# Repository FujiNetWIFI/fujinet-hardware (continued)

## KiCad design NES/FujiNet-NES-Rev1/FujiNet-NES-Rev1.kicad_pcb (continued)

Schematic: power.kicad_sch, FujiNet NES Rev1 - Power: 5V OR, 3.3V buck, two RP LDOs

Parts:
C51, C55, C56: 100nF; C_0603_1608Metric; MPN CC0603KRX7R9BB104; LCSC C14663
C52, C53, C54, C57, C58: 22uF; C_0805_2012Metric; MPN CL21A226MAQNNNE; LCSC C45783
C59, C60, C61, C62: 1uF; C_0603_1608Metric; MPN CL10A105KB8NNNC; LCSC C15849
D7: SS34; D_SMA; MPN SS34; LCSC C8678
L3: 6.8uH; L_Sunlord_SWPA4030S; MPN SWPA4030S6R8MT; LCSC C62684
Q1: AO3401A; SOT-23; MPN AO3401A; LCSC C15127
R25: 4.7k; R_0603_1608Metric; MPN 0603WAF4701T5E; LCSC C23162
U7: AP63203WU; TSOT-23-6; MPN AP63203WU-7; LCSC C780769
U8, U9: AP2112K-3.3; SOT-23-5; MPN AP2112K-3.3TRG1; LCSC C51118

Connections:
+3V3: C57.1, C58.1, L3.2, U7.1 (FB); also elsewhere on the board
+3V3_RP: C60.1, U8.5 (VOUT); also elsewhere on the board
+3V3_RPB: C62.1, U9.5 (VOUT); also elsewhere on the board
+5V: C52.1, C53.1, C54.1, C55.1, C59.1, C61.1, D7.1 (K), Q1.2 (S), U7.2 (EN), U7.3 (IN), U8.1 (VIN), U8.3 (EN), U9.1 (VIN), U9.3 (EN); also elsewhere on the board
BUCK_BST: C56.2, U7.6 (BST)
BUCK_SW: C56.1, L3.1, U7.5 (SW)
CONS_5V: C51.1, Q1.3 (D); also elsewhere on the board
GND: C51.2, C52.2, C53.2, C54.2, C55.2, C57.2, C58.2, C59.2, C60.2, C61.2, C62.2, R25.2, U7.4 (GND), U8.2 (GND), U9.2 (GND); also elsewhere on the board
VBUS: D7.2 (A), Q1.1 (G), R25.1; also elsewhere on the board

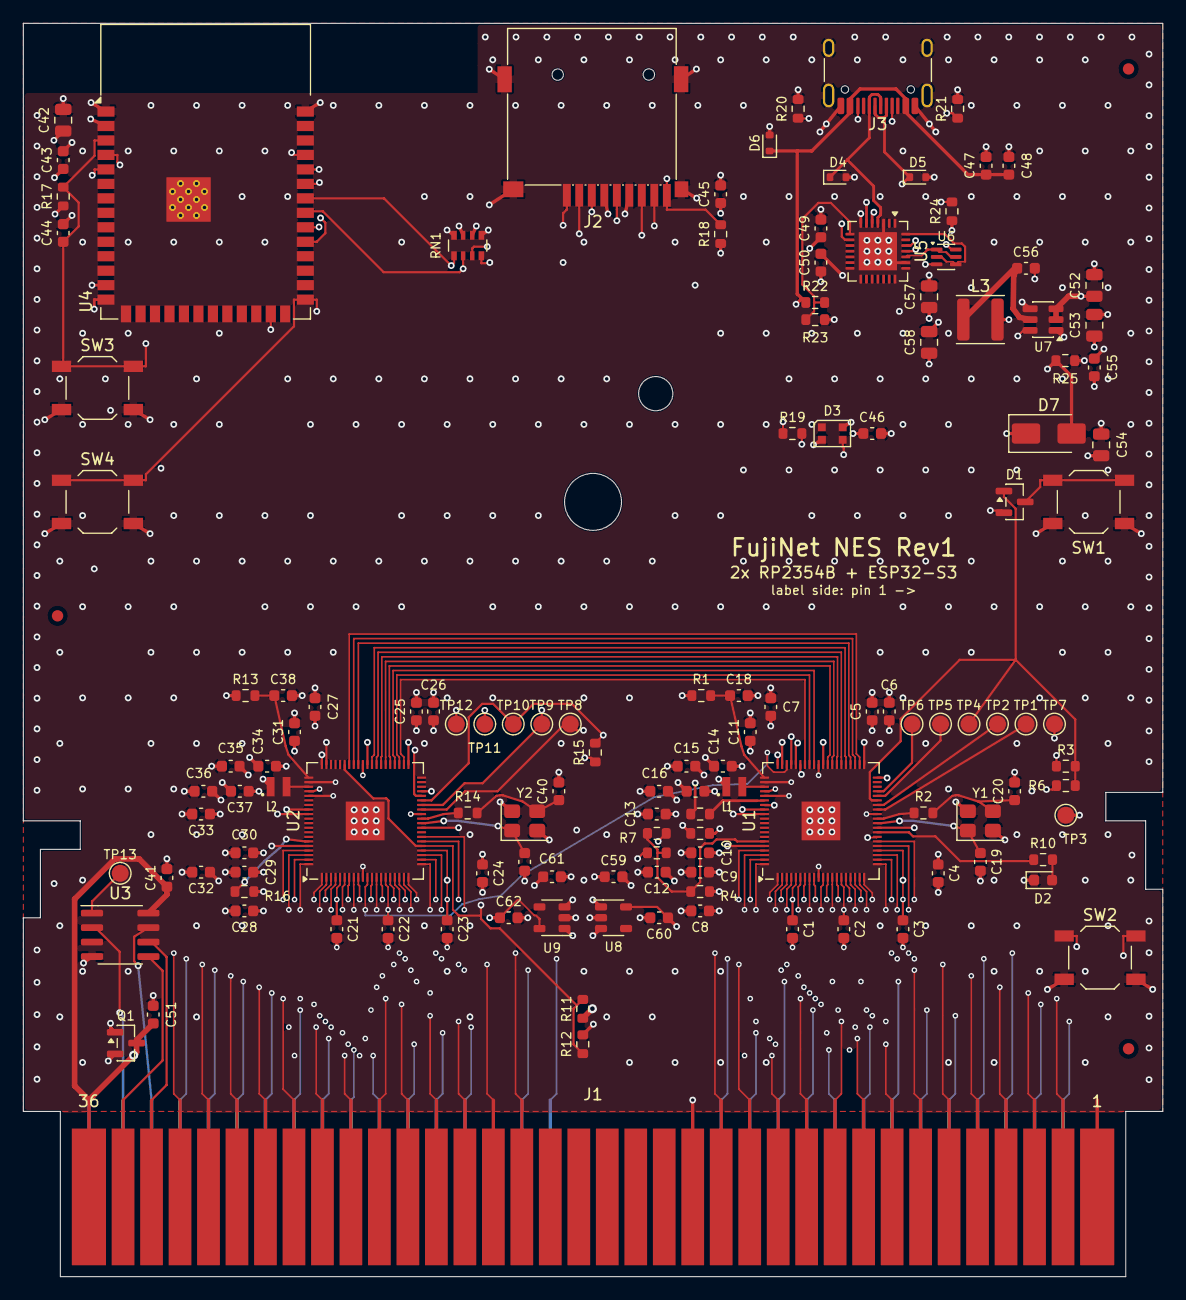
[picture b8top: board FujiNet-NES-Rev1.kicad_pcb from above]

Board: 6 copper layers, 100.0 x 110.0 mm, 133 parts (0 on the bottom side), 134 nets.

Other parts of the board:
FID1, FID2, FID3: Fiducial_1mm_Mask2mm

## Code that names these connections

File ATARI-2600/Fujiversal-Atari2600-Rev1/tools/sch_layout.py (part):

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    P = lambda n: sh.P(U, n)
    gp = lambda g: sh.P(U, D.RP_GPIO_PIN[g])
    xg = gp(2)[0]                                       # the GPIO column (pin ends), facing left
    # ---- the edge, level with GPIO2..22
    jx = X - 78.74
    sh.place(J, jx, 0)
    jy = gp(2)[1] - sh.N(J, 'CA0')[1]                    # A0 level with GPIO2
    sh.place(J, jx, jy, fields='left')
    sh.sup(sh.P(J, 23), 'CONS_5V')
    g1, g2 = sh.P(J, 12), sh.P(J, 24)
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        y = by + 5.08 * k
        sh.bus((bx, y), (bx + 7.62, y))
        sh.glabel(Pt_(bx + 7.62, y, 1, 0), name, 'R', shape)
    # ---- debug UART (GPIO0/1) up to two test pads, above the bus
    for g, x, tp, fl in ((0, xg - 5.08, 'TP_TX', 'left'), (1, xg - 15.24, 'TP_RX', 'left')):
        p = gp(g)
        sh.wire(p, (x, p[1]), (x, Y - 50.8))
        sh.place(K[tp], x, Y - 50.8, fields=fl)
    sh.name((xg - 5.08, Y - 45.72), 'RP_TX', 'R', 'R')
    sh.name((xg - 15.24, Y - 45.72), 'RP_RX', 'L', 'L')
    # ---- below the bus: the activity LED (GPIO25) and the console 5 V sense (GPIO27)
    p = gp(25)
    x = xg - 12.7
    rl, dl = K['R_LED'], K['D_LED']
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    sh.name(sh.P(rl, 2), 'RP_LED_A', 'L', 'L')
    p = gp(27)
    sh.wire(p, (xg - 5.08, p[1]), (xg - 5.08, Y + 40.64))
    sh.glabel(Pt_(xg - 5.08, Y + 40.64, 0, 1), 'VSENSE', 'D', 'input')
    for g in (23, 24, 26, 28, 29):
        sh.nc(gp(g))
    # ---- supplies across the top: the +3V3_RP rail and its decoupling row (right),
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    sh.wire(*sorted({(q[0], ry) for q in rail_pins} | {(av[0], ry)} | {(x, ry) for x in xs}))
    sh.sup((rail_pins[0][0], ry), '+3V3_RP')
    # core regulator: LX up and left through the inductor, DVDD on to its caps;
    # FB and the DVDD pins join that node
    lx, fb, dv = P(48), P(50), P(6)
    ly = top - 25.4
    L = K['L_VREG']
    sh.place(L, lx[0] - 7.62, ly, rot=90, fields='below')         # pin 1 (DVDD) left, pin 2 (LX) right
    sh.wire(lx, (lx[0], ly), sh.P(L, 2))
    dcaps = [K[k] for k in ('C_VOUT', 'C_DVDD39', 'C_DVDD6', 'C_DVDD23')]
    node = (dv[0] - 10.16, ly)
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    sh.place(D1, xr + 20.32, ry_ - 7.62, rot=180, mirror='y', fields='below')   # A1 left, A2 right, K up
    sh.wire(pts[1], sh.P(D1, 1))
    sh.wire(sh.P(D1, 2), (col, sh.P(D1, 2)[1]))
    sh.glabel((col, sh.P(D1, 2)[1]), 'S3_EN', 'R', 'bidirectional')
    k = sh.P(D1, 3)
    sw = K['SW_RESET']
    sh.place(sw, xr + 27.94, ry_ - 17.78, fields='above')
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    sh.gnd((xr + 38.1, ry_ - 17.78))
    sh.name((k[0], ry_ - 15.24), 'RST_BTN', 'R', 'R')
    rc = K['R_RUNCTL']
    sh.place(rc, pts[2][0] + 3.81, ry_, rot=270, fields='above')     # pin 2 (RUN) left, pin 1 right
    sh.wire(pts[2], sh.P(rc, 2))
    sh.wire(sh.P(rc, 1), (col, ry_))
    sh.glabel((col, ry_), 'RUN_CTL', 'R', 'input')
    sh.name((xr + 2.54, ry_), 'RUN', 'D', 'R')
    # USB to the S3: 27R series pair
    for pin, r, net, rnet, d in ((51, 'R_USBM', 'USB_DM', 'RP_USB_DM', 'U'), (52, 'R_USBP', 'USB_DP', 'RP_USB_DP', 'D')):
        p = P(pin)
        rr = K[r]
        sh.place(rr, xr + 38.1, p[1], rot=270, fields='above' if pin == 51 else 'below')
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    sh.place(sc, pts[2][0] + 3.81, q, rot=270, fields='above')
    sh.wire(pts[2], sh.P(sc, 2))
    sh.wire(sh.P(sc, 1), (col, q))
    sh.glabel((col, q), 'BOOTSEL_CTL', 'R', 'input')
    for n in (55, 56, 57, 58, 59):
        sh.nc(P(n))
    # 12 MHz crystal: XIN straight to the crystal and its load cap, XOUT through the 1k
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    g2 = sh.P(Yc, 2)
    sh.wire(g2, (g2[0] + 2.54, g2[1]))
    sh.gnd((g2[0] + 2.54, g2[1]))
    sh.place(rx, xr + 10.16, xo[1], rot=90, fields='above')        # pin 1 (XOUT) left
    sh.wire(xo, sh.P(rx, 1))
    sh.wire(sh.P(rx, 2), (cx, xo[1]), sh.P(Yc, 3))
    sh.place(c2, cx, xo[1] + 3.81, fields='right')
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    en = sh.P(U, 3)
    ey = 109.22
    sh.wire(en, (170.18, en[1]), (170.18, ey), (162.56, ey), (152.4, ey), (142.24, ey), (127.0, ey))
    sh.glabel((127.0, ey), 'S3_EN', 'L', 'bidirectional')
    sh.place(K['R_EN'], 162.56, ey - 3.81, fields='right')
    sh.sup(sh.P(K['R_EN'], 1), '+3V3')
    sh.place(K['C_EN'], 152.4, ey + 3.81, fields='right')
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    # IO0 (BOOT): button + the auto-program transistor
    io0 = sh.P(U, 27)
    sh.wire(io0, (147.32, io0[1]), (137.16, io0[1]))
    sh.glabel((137.16, io0[1]), 'S3_IO0', 'L', 'bidirectional')
    sh.place(K['SW_S3BOOT'], 147.32, io0[1] + 5.08, rot=270, fields='left')
    sh.gnd(sh.P(K['SW_S3BOOT'], 2))
    # IO4 / IO5: RUN / BOOTSEL of the RP2354A
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    sh.place(K['R_CPRST'], 172.72, rst[1] - 3.81, fields='left')
    sh.wire(rst, (172.72, rst[1]), (167.64, rst[1]))
    sh.sup(sh.P(K['R_CPRST'], 1), '+3V3')
    sh.glabel((167.64, rst[1]), 'CP_RST', 'L')
    sh.gnd(sh.P(U, 3))
    sh.gnd(sh.P(U, 23), 2.54, rot=90)                      # /CTS tied low
    nc_unused(sh, U)
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    gq = sh.P(K['C_CONS'], 2)
    sh.wire(gq, (gq[0] - 5.08, gq[1]))
    sh.flag((gq[0] - 5.08, gq[1]), 'GND')
    # console 5 V sense for the RP (GPIO27): 0.6 x CONS_5V, filtered
    vh, vl, vc = K['R_VSH'], K['R_VSL'], K['C_VS']
    sh.place(vh, 53.34, y5 - 7.62 - 3.81, rot=180, fields='left')   # pin 1 (CONS_5V) down
    sh.wire((53.34, y5), sh.P(vh, 1))
    nd = sh.P(vh, 2)
    vy = nd[1] - 2.54
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    sh.gnd(sh.P(vl, 2))
    sh.place(vc, 73.66, vy + 3.81, fields='right')
    sh.gnd(sh.P(vc, 2))
    sh.glabel((83.82, vy), 'VSENSE', 'R', 'output')
    # USB VBUS -> gate, and through the SS34 onto +5V
    Dv = K['D_VBUS']
    sh.place(Dv, 83.82, yv, rot=180, fields='below')
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
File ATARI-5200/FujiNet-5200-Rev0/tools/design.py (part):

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RP_IO_RAIL = '+3V3_RP'     # IOVDD x8, QSPI_IOVDD, USB_OTP_VDD, ADC_AVDD: the fast LDO
RP_CORE_RAIL = RP_IO_RAIL  # VREG_VIN (+ VREG_AVDD through 33R) on the same LDO rail

# a52_cart.h.  GPIO0-31 are the 5 V-tolerant bus inputs; GPIO40-47 are not and carry only the ADC
# sense and the 3.3 V debug header.
RP_GPIO_NET = {i: 'A%d' % i for i in range(14)}                     # A0_PIN 0: A0-A13
RP_GPIO_NET.update({14: 'EN40_N', 15: 'EN80_N'})                    # EN40_PIN, EN80_PIN
RP_GPIO_NET.update({16 + i: 'RP_D%d' % i for i in range(8)})        # D0_PIN 16: into the '541
RP_GPIO_NET.update({24: 'PWR_OK', 25: 'PHI2_RP', 26: 'BUF_EN', 27: 'RP_LED', 28: 'ILK'})
RP_GPIO_NET.update({g: NC for g in range(29, 40)})
RP_GPIO_NET.update({40: 'VSENSE_ADC', 41: NC, 42: NC, 43: NC, 44: 'DBG_TX', 45: 'DBG_RX', 46: NC, 47: NC})
assert len(RP_GPIO_NET) == 48 and set(RP_GPIO_NET) == set(RP_GPIO_PIN)

# ESP32-S3-WROOM-1 module pad -> function (pads per the KiCad symbol)
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      70: NC, 71: NC, 72: NC, 73: NC, 74: NC,                                 # QSPI (flash in package)
      75: 'QSPI_SS', 81: 'GND'}
rp.update({p: RP_IO_RAIL for p in RP_IOVDD_PINS})
rp.update({p: 'DVDD' for p in RP_DVDD_PINS})
for g, pin in RP_GPIO_PIN.items():
    rp[pin] = RP_GPIO_NET[g]
U_RP = add('U', '%s:RP2354B_Split' % LIB, 'RP2354B', FP('QFN-80-1EP_10x10mm_P0.4mm_EP3.4x3.4mm'), rp,
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U_RP.unit_sheets = {1: 'cart-bus', 2: 'rp-core'}
U_RP.pin_unit = {str(pad): 1 if pad in RP_GPIO_PIN.values() else 2 for pad in rp}

# -- the data path: the RP puts each byte on GPIO16-23, a 74HCT541 that only the enables open puts
# it on D0-D7 (a52_cart.h: software is never between an enable and the data).  Its eight channels
# are identical, so they are used in reverse (bit k on channel 8-k: A8 / Y8 carry D0): turned 270
# degrees over the D0-D7 fingers, the '541's Y row (pins 11-18) then meets the fingers in their own
# left-to-right order and its A row (pins 9-2) the RP2354B's GPIO16-23 corner in theirs -- the data
# path from the slot to the RP crosses nothing (gen_pcb.buf_fanin draws the finger side).
buf = {1: 'SERVE_N', 19: 'EN_ANY_N', 10: 'GND', 20: '+5V'}     # /OE1, /OE2 (equivalent: drive = !OE1 & !OE2)
buf.update({9 - i: 'RP_D%d' % i for i in range(8)})             # A8..A1 (pins 9..2) = bit 0..7
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# -- PHI2 (edge 14): GND on CA018087; on the universal boards PHI2 through a 74LS125 and CR9 (1N914,
# anode at pin 14), so the console only pulls it low, to VOL(LS125) + VF(1N914) <= ~1.15 V: over the
# RP2350's VIL of 0.8 V (Table 1436).  A 74LVC1G17 Schmitt on +5V reads it (VT- >= 1.32 V at VCC
# 4.5 V, Nexperia 74LVC1G17 Table 8) and drives GPIO25 (5 V tolerant).  The pull-up comes from the
# console's own 5 V, so nothing is pushed into an unpowered console; 4.7k reaches VT+ in ~60 ns.
R('4.7k', 'CONS_5V', 'PHI2', desc='PHI2 pull-up (the console drives pin 14 only low, through a diode)',
  key='R_PHI2PU')
add('U', '74xGxx:74LVC1G17', '74LVC1G17', FP('SOT-353_SC-70-5'), {1: NC, 2: 'PHI2', 3: 'GND', 4: 'PHI2_RP',
    5: '+5V'}, mpn='74LVC1G17GW,125', lcsc='C426705', desc='PHI2 Schmitt buffer: CMOS thresholds for the '
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       key='JP_ILK')
# DNP: a firmware-controlled interlock (a console power cycle = its only reset).  The jumper sits at
# ground potential when closed, so the switch is an N-FET on the low side: D on CI2 (pin 36), S on CI1
# (pin 18), gate pulled up to +5V (closed whenever the cart has power); GPIO28 high turns Q_ILKDRV on
# and opens it.  Needs the cart powered from USB or the edge's raw DC once JP_ILK is cut.
NFET('ILK_G', 'ILK_A', 'ILK_B', 'interlock switch (DNP): D = CI2 (pin 36), S = CI1 (pin 18)', dnp=True,
     key='Q_ILK')
R('10k', '+5V', 'ILK_G', desc='interlock switch closed by default (DNP)', dnp=True, key='R_ILKG')
NFET('ILK', 'GND', 'ILK_G', 'interlock switch driver, G = GPIO28: high opens the interlock (DNP)', dnp=True,
     key='Q_ILKDRV')
R('4.7k', 'ILK', 'GND', desc='GPIO28 low until the firmware drives it (RP2350-E9: <= 8.2k; DNP)', dnp=True,
  key='R_ILKPD')
# -- VR1 (the console 5 V that feeds the cart) for the ADC (GPIO40, not 5 V tolerant): 100k / 100k =
# 0.5 x, 5.5 V reads 2.75 V; 100 nF for the ADC's sample capacitor
R('100k', 'CONS_5V', 'VSENSE_ADC', desc='console 5V -> ADC divider (0.5 x)', key='R_ADCH')
R('100k', 'VSENSE_ADC', 'GND', desc='console 5V -> ADC divider', key='R_ADCL')
C('100nF', 'VSENSE_ADC', desc='ADC sample reservoir', key='C_ADCF')
# -- activity LED straight off GPIO27 (3.3 V): red, ~1.3 mA
R('1k', 'RP_LED', 'RP_LED_A', desc='activity LED series', key='R_LED')
add('D', 'Device:LED', 'red', FP('LED_0603_1608Metric'), {1: 'GND', 2: 'RP_LED_A'},
    mpn='KT-0603R', lcsc='C2286', desc='activity LED (GPIO27)', key='D_LED')
# -- debug UART (GPIO44 TX, GPIO45 RX; 3.3 V only), DNP: fit for bring-up
add('J', 'Connector_Generic:Conn_01x03', 'DBG UART', FP('PinHeader_1x03_P2.54mm_Vertical'),
    {1: 'DBG_TX', 2: 'DBG_RX', 3: 'GND'}, mpn='PZ254V-11-03P', lcsc='C2937625',
    desc='RP debug UART, 3.3 V: 1 TX (GPIO44), 2 RX (GPIO45), 3 GND; fit for bring-up', dnp=True, key='J_DBG')
# -- bring-up pads: the enables, PHI2 and the '541's two enables, PWR_OK, with a scope ground
TP('EN40_N', '/EN40', desc='scope pad: console /Enable $40-$7F', key='TP_EN40')
TP('EN80_N', '/EN80', desc='scope pad: console /Enable $80-$BF', key='TP_EN80')
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C('10uF', RP_IO_RAIL, desc='RP IO rail bulk (LDO output)', key='C_IOBULK')
C('4.7uF', RP_CORE_RAIL, desc='VREG_VIN bulk (LDO rail)', key='C_VREGIN')
for pin in RP_DVDD_PINS:
    C('100nF', 'DVDD', desc='DVDD decoupling', key='C_DV%d' % pin)
C('4.7uF', 'DVDD', desc='core regulator output', key='C_DVBULK')
R('33R', RP_CORE_RAIL, 'VREG_AVDD', desc='VREG_AVDD filter', key='R_AVDD')
C('4.7uF', 'VREG_AVDD', desc='VREG_AVDD filter', key='C_AVDD')
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SW('RESET', 'RST_BTN', 'cart RESET: RP RUN + S3 EN via BAT54C', key='SW_RESET')
add('D', 'Diode:BAT54C', 'BAT54C', FP('SOT-23'), {1: 'RUN', 2: 'S3_EN', 3: 'RST_BTN'},
    mpn='BAT54C,215', lcsc='C37704', desc='RESET steering, common cathode', key='D_RST')
# RUN / BOOTSEL: the S3 drives them low to assert (fnPicoUpdater::forceBootselViaPins)
R('10k', RP_IO_RAIL, 'RUN', desc='RUN pull-up', key='R_RUN')
R('10k', RP_IO_RAIL, 'QSPI_SS', desc='QSPI_SS pull-up', key='R_SS')
R('1k', 'QSPI_SS', 'BOOTSEL_BTN', desc='BOOTSEL button series', key='R_BSEL')
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
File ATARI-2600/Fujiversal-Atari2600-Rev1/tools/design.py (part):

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~/Workspace/fn-2600):
  pico/atari-2600/firmware/include/vcs_pins.h       A0-A12 GP2-14, D0-D7 GP15-22
  pico/atari-2600/firmware/boards/fujivcs.h         LED = PICO_DEFAULT_LED_PIN (GP25)
  include/pinmap/fujiversal-atari2600.h             S3 pins (SD, LED, UART0, RUN/BOOTSEL)
Edge pinout: the standard 2600 24-pin cartridge port; geometry and face
orientation from the FujiPlusCart prototype gerbers (make_edge_fp.py).

What changed from Rev0 (RP2040 + W25Q16 + 3x 74LVC245A):
  * RP2354A (RP2350A + 2 MB flash stacked in the package), wired straight to
    the 5 V edge.  Its GPIO0-25 are "Digital IO (FT)": they tolerate 5.5 V
    while IOVDD is 3.3 V (RP2350 datasheet, pin types / VPIN_FT), and a 3.3 V
    high clears the 6507's TTL VIH (2.0 V).  No buffers, so no DIR pin: the
    firmware's per-access output enable (DATA_DRIVE / DATA_RELEASE) is the
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# vcs_pins.h: ADDR_PIN 2 (A0-A12), D0_PIN 15 (D0-D7); fujivcs.h: LED GP25
RP_GPIO_NET = {2 + i: 'CA%d' % i for i in range(13)}
RP_GPIO_NET.update({15 + i: 'CD%d' % i for i in range(8)})
RP_GPIO_NET.update({0: 'RP_TX', 1: 'RP_RX', 23: NC, 24: NC, 25: 'RP_LED',
                    26: NC, 27: 'VSENSE', 28: NC, 29: NC})
assert set(RP_GPIO_NET) == set(RP_GPIO_PIN)
# Only the FT pins may meet the 5 V bus: GPIO26-29 are the ADC pins (VPIN max IOVDD + 0.5 V)
assert all(g <= 25 for g, n in RP_GPIO_NET.items() if n and n[:2] in ('CA', 'CD'))

# ESP32-S3-WROOM-1 module pad -> function (pads per the KiCad symbol)
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          'IO47': 24, 'IO48': 25, 'IO45': 26, 'IO0': 27, 'IO35': 28,
          'IO36': 29, 'IO37': 30, 'IO38': 31, 'IO39': 32, 'IO40': 33,
          'IO41': 34, 'IO42': 35, 'RXD0': 36, 'TXD0': 37, 'IO2': 38, 'IO1': 39}
# include/pinmap/fujiversal-atari2600.h + the fujiversal RUN/BOOTSEL forcing contract (IO4/IO5)
S3_NET = {'EN': 'S3_EN', 'IO0': 'S3_IO0', 'IO4': 'RUN_CTL', 'IO5': 'BOOTSEL_CTL',
          'IO19': 'USB_DM', 'IO20': 'USB_DP', 'IO38': 'SD_MOSI', 'IO39': 'SD_SCK',
          'IO40': 'SD_MISO', 'IO41': 'SD_CS', 'IO42': 'SD_CD', 'IO48': 'LED_STRIP',
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    bom=False, key='J_EDGE')
# -- RP2354A.  RP2350 datasheet section 6.3.7 Figure 19 ("combined supplies"):
# VREG_VIN and VREG_AVDD (through 33R) from one 3.3 V supply, 3.3 uH + 4.7 uF
# core regulator; DVDD 100 nF on the two pins nearest the regulator (39, 6),
# 4.7 uF on the far one (23).  The regulator corner is Raspberry Pi's own
# RP2350A minimal-design layout (0402 parts, gen_pcb.py grafts it).
rp = {21: 'XIN', 22: 'XOUT', 24: 'SWCLK', 25: 'SWDIO', 26: 'RUN',
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      55: NC, 56: NC, 57: NC, 58: NC, 59: NC,                       # QSPI data/clock: the flash is in the package
      60: 'QSPI_SS', 61: 'GND'}
rp.update({p: RP_RAIL for p in RP_IOVDD_PINS})
rp.update({p: 'DVDD' for p in RP_DVDD_PINS})
for g, pin in RP_GPIO_PIN.items():
    rp[pin] = RP_GPIO_NET[g]
add('U', 'MCU_RaspberryPi:RP2354A', 'RP2354A', FP('RPI_RP2350A_QFN60'), rp,
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add('L', 'Device:L', '3.3uH', FP('RPI_L_AOTA-B201610S3R3'), {1: 'DVDD', 2: 'RP_LX'},
    mpn='AOTA-B201610S3R3-101-T', lcsc='C42411119', desc='RP2350 core SMPS inductor (polarity marked)', key='L_VREG')
C('4.7uF/0402w', 'DVDD', desc='core regulator output (C_OUT)', key='C_VOUT')
C('100nF', 'DVDD', desc='DVDD decoupling (pin 39)', key='C_DVDD39')
C('100nF', 'DVDD', desc='DVDD decoupling (pin 6)', key='C_DVDD6')
C('4.7uF', 'DVDD', desc='DVDD decoupling (pin 23, far from the regulator)', key='C_DVDD23')
# 12 MHz crystal (minimal design: ABM8-272-T3, 15 pF loads, 1k in XOUT)
add('Y', 'Device:Crystal_GND24', '12MHz', FP('Crystal_SMD_3225-4Pin_3.2x2.5mm'),
    {1: 'XIN', 2: 'GND', 3: 'XOUT_Y', 4: 'GND'}, mpn='ABM8-272-T3', lcsc='C20625731', key='Y_XTAL')
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SW('RESET', 'RST_BTN', 'cart RESET: RP RUN + S3 EN through the BAT54C', key='SW_RESET')
add('D', 'Diode:BAT54C', 'BAT54C', FP('SOT-23'), {1: 'RUN', 2: 'S3_EN', 3: 'RST_BTN'},
    mpn='BAT54C,215', lcsc='C37704', desc='RESET steering, common cathode', key='D_RST')
# RUN / BOOTSEL, forced by the S3 exactly as fnPicoUpdater::forceBootselViaPins()
# expects: its pins idle as inputs and drive LOW to assert, so with 3.3 V on
# both chips a 1k series resistor is the whole interface.
R('10k', RP_RAIL, 'RUN', desc='RUN pull-up', key='R_RUNPU')
R('1k', 'RUN_CTL', 'RUN', desc='S3 IO4 -> RP RUN (low = reset)', key='R_RUNCTL')
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R('4.7k', 'VBUS', 'GND', desc='P-FET gate pull-down against the SS34 reverse leakage', key='R_VBPD')
C('10uF', 'CONS_5V', desc='edge 5V bulk', key='C_CONS')
C('100nF', 'CONS_5V', desc='edge 5V HF bypass', key='C_CONSHF')
# console 5 V sense for the RP (VSENSE -> GPIO27): GP27 is an ADC pin (not FT), so the divider keeps it under
# IOVDD: 3.0 V at 5.0 V, 3.15 V at 5.25 V; 100 nF makes it a ~6 ms filter
R('100k', 'CONS_5V', 'VSENSE', desc='console 5V sense divider', key='R_VSH')
R('150k', 'VSENSE', 'GND', desc='console 5V sense divider (0.6 x CONS_5V)', key='R_VSL')
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
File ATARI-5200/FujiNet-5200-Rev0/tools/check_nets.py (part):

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      PIN_RP2040_RUN/BOOTSEL when the pinmap does not define them
and checks every GPIO of both chips against the pin *functions* the netlist reports (GPIOn on
the RP2354B, IOn on the S3, An/Yn on the '541), the 5200 36-pin edge map (its own copy of the
pinout, from Atari's CX5200 Field Service Manual), the 5 V-tolerance rule for GPIO40-47, the PHI2
buffer, the supply sense dividers, the interlock, the three-source power path, and the edge
footprint's faces, pin-1 end and short interlock fingers.  The enable logic itself is
check_glue.py's.
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    chk('GP%d (PHI2_RP): the RP and the buffer only' % P['PHI2'], not others(rp(P['PHI2']), {U1, U17} | tps))

    # ---- the RP's own outputs and inputs ----
    pwr_ok_pin = rp(P['PWROK'])
    bufen = rp(P['BUFEN'])
    chk('GP%d (BUF_EN) -> a 74HCT glue input' % P['BUFEN'], glue_in(bufen))
    pd = pulldown(bufen)
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        hdr is not None and node_net.get((hdr, '1')) == rp(P['DBG_TX']) and node_net.get((hdr, '2')) == rp(P['DBG_RX'])
        and node_net.get((hdr, '3')) == 'GND')

    # ---- interlock: 18-36 shorted by the solder jumper; the DNP low-side switch from GPIO28 beside it ----
    ia, ib = edge[18], edge[36]
    jp = [r for r, (v, fp) in parts.items() if r.startswith('JP') and
          {node_net.get((r, '1')), node_net.get((r, '2'))} == {ia, ib}]
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            all(r in dnp for r in [r for r in parts if re.match(r'R\d+$', r) and through_r(gate, v5) and
                                   {node_net.get((r, '1')), node_net.get((r, '2'))} == {gate, v5}]))

    # ---- GPIO40-47 are not 5 V tolerant: the ADC sense or the 3.3 V debug header only ----
    for g in range(40, 48):
        n = rp(g)
        if unconn(n):
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        chk('GP%d (%s): nothing but passives or the 3.3 V debug header on the net' % (g, n), not bad)
        chk('GP%d (%s): never an edge signal' % (g, n), n not in edge.values())

    # ---- supply sense: edge pin 26 (VR1) -> divider -> ADC (GPIO40) ----
    cons = sig['PWR']
    adc = rp(P['VSENSE'])
    top, bot = through_r(cons, adc), through_r(adc, 'GND')
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            'current)' % (5.25 * r), 5.25 * r < VCC_MIN)
    pwr_ok = inv(inv(vsense))
    chk('PWR_OK = !!VSENSE on the Schmitt', pwr_ok is not None)
    chk('PWR_OK -> GP%d' % P['PWROK'], pwr_ok == pwr_ok_pin)
    chk('PWR_OK -> the glue', glue_in(pwr_ok))
    for r in sorted(glue):
        vcc, gnd = ('20', '10') if r == BUF else ('5', '3') if r == U17 else ('14', '7')
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    chk('RP USB_DP -> 27R -> S3 USB_D+ (IO20)', through_r(func_net.get((U1, 'USB_DP')), func_net.get((S3, 'USB_D+'))) == '27R')
    chk('RP USB_DM -> 27R -> S3 USB_D- (IO19)', through_r(func_net.get((U1, 'USB_DM')), func_net.get((S3, 'USB_D-'))) == '27R')
    print('note: S3 pins from %s' % PINMAP)
    run_io, bsel_io = define(PINMAP, 'PIN_RP2040_RUN', -2), define(PINMAP, 'PIN_RP2040_BOOTSEL', -2)
    if run_io == -2 or bsel_io == -2:
        run_io, bsel_io = define(PINMAP_RUN, 'PIN_RP2040_RUN'), define(PINMAP_RUN, 'PIN_RP2040_BOOTSEL')
        print('note: %s does not define PIN_RP2040_RUN/BOOTSEL; using fujiversal-intv.h (IO%d/IO%d)'
              % (os.path.basename(PINMAP), run_io, bsel_io))
    run, ss = func_net.get((U1, 'RUN')), func_net.get((U1, '~{QSPI_SS}'))
    chk('S3 IO%d (PIN_RP2040_RUN) -> 1k -> RP RUN' % run_io, through_r(s3(run_io), run) == '1k')
    chk('S3 IO%d (PIN_RP2040_BOOTSEL) -> 1k -> RP QSPI_SS' % bsel_io, through_r(s3(bsel_io), ss) == '1k')
    chk('RUN pull-up to the IO rail', through_r(run, v33io) == '10k')
    chk('QSPI_SS pull-up to the IO rail', through_r(ss, v33io) == '10k')
    for f in ('QSPI_SCLK', 'QSPI_SD0', 'QSPI_SD1', 'QSPI_SD2', 'QSPI_SD3'):
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            if ref == U1 and f in ('IOVDD', 'QSPI_IOVDD', 'USB_OTP_VDD', 'ADC_AVDD', 'VREG_VIN'):
                chk('RP %s (pin %s) on %s' % (f, pin, v33io), n == v33io)
            if ref == U1 and f == 'DVDD':
                chk('RP DVDD (pin %s) on DVDD' % pin, n == func_net.get((U1, 'VREG_FB')))
            if ref == U1 and f in ('GND', 'VREG_PGND'):
                chk('RP %s (pin %s) on GND' % (f, pin), n == 'GND')
    for f in ('SWCLK', 'SWDIO', 'RUN'):
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
    # ---- S3 pins: the pinmap ----
    sd = {k: define(PINMAP, 'PIN_SD_HOST_' + k) for k in ('CS', 'SCK', 'MISO', 'MOSI')}
    led_strip = define(PINMAP, 'PIN_LED_STRIP')
    uart_rx, uart_tx = define(PINMAP, 'PIN_UART0_RX'), define(PINMAP, 'PIN_UART0_TX')
    card = define(PINMAP, 'PIN_CARD_DETECT', -1)
    chk('SD CS  IO%d -> microSD DAT3/CS' % sd['CS'], s3(sd['CS']) == node_net.get((J2, '2')))
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              '(pulled up) as the 7800 / NES / SMS boards do, unused by the firmware' % (os.path.basename(PINMAP), cd_io))
    ws_din = node_net.get((WS, '3'))
    chk('LED strip IO%d -> R -> WS2812 DIN' % led_strip, through_r(s3(led_strip), ws_din) is not None)
    chk('PIN_UART0_TX/RX are the module TXD0/RXD0 pads (GPIO43/44)', (uart_tx, uart_rx) == (43, 44))
    chk('S3 TXD0 -> CP2102N RXD', func_net.get((S3, 'TXD0')) == func_net.get((UCP, 'RXD')))
    chk('S3 RXD0 <- CP2102N TXD', func_net.get((S3, 'RXD0')) == func_net.get((UCP, 'TXD')))
    contract = set(sd.values()) | {led_strip, run_io, bsel_io, 19, 20, 0} | ({card} if card >= 0 else {cd_io})
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
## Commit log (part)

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2020-05-10 Add schematics
2020-05-15 Fix cut off WROVER schematic
2020-05-25 Update WROVER schematic with some notes
2020-06-07 Schematics: Add v1.0 schematic and rename all so they are in order by date.
2020-07-05 Add CC-BY-SA LICENSE
2020-07-05 Add FujiNet 1.0 dir with 3D designs & schematic, move old schematics to Prototype dir
2020-07-17 Add PCB 3D files
2020-08-11 Reduce SIO Receptacle depth by 1.75mm
2020-08-11 Add 1.0 PCB 3D files
2020-08-11 Add official and complete FujiNet 1.0 design files
2020-08-15 Add OSHWA certification info and logos to PCB
2020-08-15 Update logo mark with missing 0 in UID
2020-08-18 Add SIO pin part numbers to BOM
2020-09-02 Add Diptrace libraries
2020-12-25 Add v1.3 hardware design. Fixes #1, #2, #3
2021-01-02 Update v1.3 README
2021-01-02 Update v1.3 Plug with added support for pins & no longer has domed holes on the mating end.
2021-01-15 Add image of bodge for issue #5
2021-01-15 Fix CP2102 Reset bug in v1.3 design
2021-01-15 Update README and CP2102 fix image cuz I can't count
2021-01-16 Add v1.3 PCB STEP file
2021-01-24 Add resistor divider fix for v1.3 board
2021-02-13 Update v1.3 fix information
2021-03-14 Add v1.5 design files. Fixes #5. Move old versions to subdir
2021-03-14 More file cleanup
2021-03-14 Update schematic & README: Reduce capacitance for auto-reset/EN
2021-03-28 Add Diptrace library for Commodore patterns
2021-03-28 Add Diptrace component library for Commodore ports
2021-04-11 More descriptive change log
2021-05-03 Fujinet Version 1.0: Added insert for plug to minimize possibility of ping breaking when not evenly inserted.
2021-10-14 Add FujiNet576NUC design files
2021-11-28 Add FujiNet v1.6 design files
2021-12-15 Add Coleco ADAM prototype schematic
2022-02-24 Update ADAM schematic
2022-03-07 Add ADAM DEVKITC Schematic
2022-04-01 Rearrange dir structure to accomodate multiple platforms
2022-04-14 Add ADAM FujiNet v1.0 design
2022-06-13 Fix cut off schematic image
2022-07-23 Add FujiApple Rev00 Hardware Design
2022-07-24 A2: change resistor divider for HDSEL
2022-08-05 A2: add 3D model of Rev 00
2022-09-18 Add RS232 prototype
2022-10-06 AppleII: add DB19 Adapter
2022-10-06 Update Readme.md
    Added images
2022-12-04 Add STL files for Apple II case
2023-01-19 ATARI: add v1.7 hardware
2023-03-22 FujiApple Rev00 SPI Fix
2023-03-22 FujiaApple Rev00 SPI Fix README
2023-03-22 Add Lynx FujiNet DEVKITC Schematic
2023-06-02 Add FujiApple Rev000
2023-08-11 Add FujiLynx Prototype
2023-08-24 atari: update v1.7 XE front case, fix disconnected screw posts near sio plug
2023-11-29 Add FujiApple Rev1 Schematic
2023-12-18 Add DB19 to IDC20F Adapter
2023-12-25 Add FujiApple Rev1 hardware design files
2023-12-27 Add FujiApple Rev1 PickNPlace & BOM as CSV
2023-12-28 Update BOM CSV and Pick-N-Place File
2023-12-28 Add some JLCPCB part numbers to BOM CSV
2023-12-29 Finish adding JLCPCB part number to FujiApple BOM
2024-02-18 Add FujiApple Rev1.1
2024-02-18 Add Atari v1.7.1
2024-02-20 Fix unconnected 12V trace on Apple II DB19 Female PCB
2024-02-26 AppleII: fix link to wiki in README for hardware
2024-03-09 Reorganize Apple II and add new designs
2024-03-09 Fix docs directory
2024-03-10 Update Apple II docs
2024-03-10 Fix images links in docs
2024-03-29 Atari: add devkit-shield and move old versions
2024-03-31 Add Coco designs
2024-04-02 RC2014: Add last prototype (Rev 0.3)
2024-04-18 Add Apple Mac 68k FujiNet
2024-04-18 Add AliExpress BOM
2024-04-18 Fix README typo
2024-04-22 Rework instructions for multiple baud rate selection
2024-06-23 Mirror '2' and '40' indicators so they are readable
2024-06-23 Revert "Mirror '2' and '40' indicators so they are readable"
    This reverts commit 8205e6bc94a8408d7df05aae4ad7f4186c382163.
2024-06-23 Mirror '2' and '40' text so it is readable on the backside of the PCB
2024-08-17 Apple2: Updated DB-19 adapter to Rev1.1
2024-08-26 Add Coco Rev0000 version
2024-08-26 Move Rev000 back from Old directory to deal with merge of PCB change
2024-10-01 Fix BOM for Apple II DevKit flavors, should be LSF0204PWR (no D)
2024-10-06 Add Apple III adapter board
2024-10-06 Update Apple III adapter README
2024-10-21 Add connector sleeve for Apple III adapter
2025-02-03 Add Dragon ROM and cabling docs for CocoFuji
2025-03-01 RS232: add Rev000 with DB9F
2025-03-06 Fix images of old hardware versions
    Additionally, make resized images link to the full-size version.
    Also fixes one typo.
2025-03-14 replace level-shifter component
2025-03-14 fix naming of RS232-Rev00
2025-03-18 RS232: Update Rev000 to support both TSSOP & SSOP on same PCB
2025-09-03 Add RS232 Rev1 Hardware
2025-09-03 Add RS232 schematic image
2025-09-05 Add RS232 BOM and fix gitignore to allow CSV
2025-09-06 Add missing RS232 CSV files. Fix screw link in RS232 README
2025-09-12 Update dragon support
2025-10-22 Add RS232-Rev1b: push-push MicroSD socket
2025-11-09 [h89] add H89 hardware schematic and related datasheets and programming info.
2026-03-13 Add MSX prototype schematics and pics
2026-03-13 MSX: Update README.md
2026-03-13 MSX: Add PDF schematic to README
2026-06-15 Dragon rom update
    Suppress interrupts while processing drivewire commands to resolve issues
    with glitches on directory entry fetches etc.
